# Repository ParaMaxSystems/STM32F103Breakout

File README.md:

# STM32F103Breakout
STM32 Breakout Board with Power Stage, inspired by Phil's Lab's design. 
STM32F103C8T board with connectors for I2C, USB, SPI, and GPIO headers.
Broken out to fit vertical or horizontal connectors.
Powered by a 3.3v switching regulator, taking power from USB or Vin and
conrverting to a 3.3v power source. Can be much smaller but I don't want to.

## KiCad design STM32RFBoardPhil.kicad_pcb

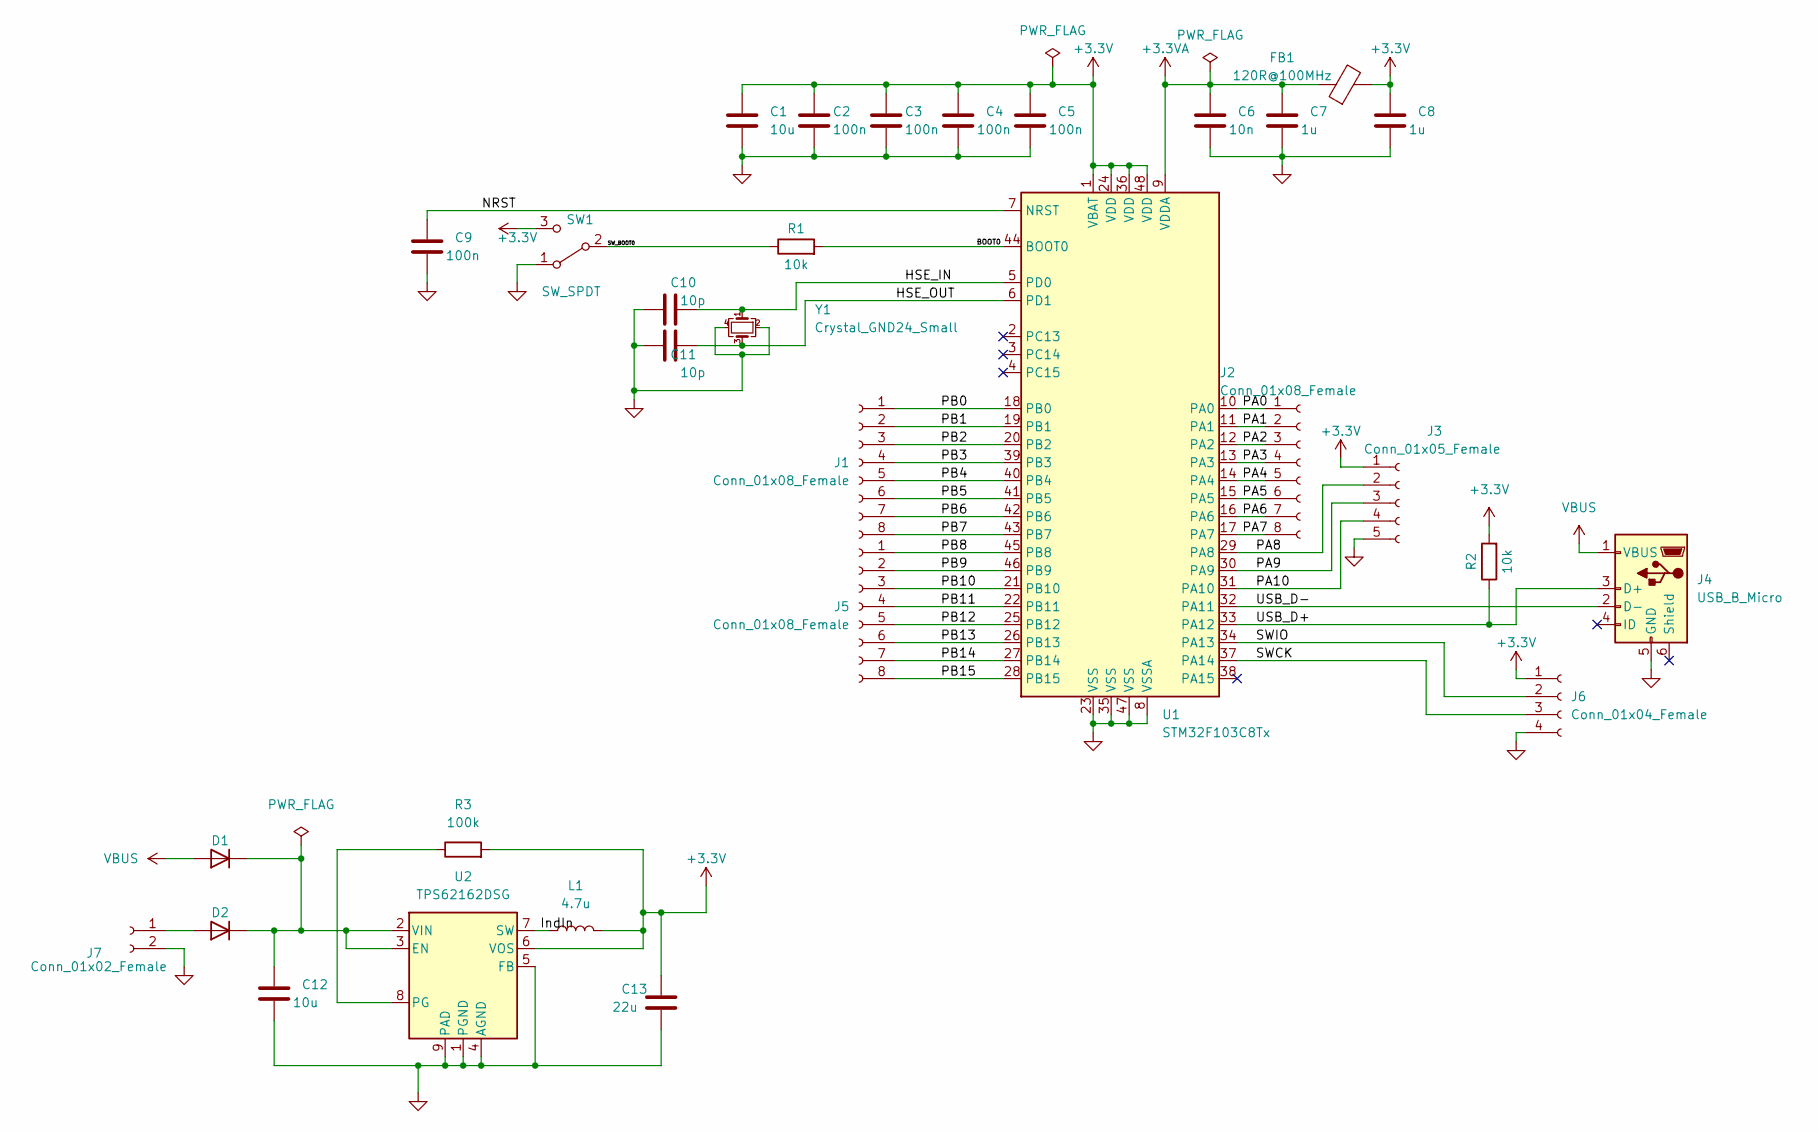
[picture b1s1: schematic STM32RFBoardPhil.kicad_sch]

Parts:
C1: 10u; C_0805_2012Metric
C2, C3, C4, C5, C9: 100n; C_0402_1005Metric
C6: 10n; C_0402_1005Metric
C7, C8: 1u; C_0402_1005Metric
C10, C11: 10p; C_0402_1005Metric
C12: 10u; C_0603_1608Metric
C13: 22u; C_0603_1608Metric
D1, D2: DIODE; D_0603_1608Metric
FB1: 120R@100MHz; L_0603_1608Metric
J1, J2, J5: Conn_01x08_Female; PinSocket_1x08_P2.54mm_Horizontal
J3: Conn_01x05_Female; PinSocket_1x05_P2.54mm_Horizontal
J4: USB_B_Micro; USB_Micro-B_Wuerth_629105150521
J6: Conn_01x04_Female; PinSocket_1x04_P2.54mm_Horizontal
J7: Conn_01x02_Female; PinSocket_1x02_P2.54mm_Vertical
L1: 4.7u; L_0805_2012Metric
R1, R2: 10k; R_0402_1005Metric
R3: 100k; R_0402_1005Metric
SW1: SW_SPDT; SW_SPDT_CK-JS102011SAQN
U1: STM32F103C8Tx; LQFP-48_7x7mm_P0.5mm
U2: TPS62162DSG; WSON-8-1EP_2x2mm_P0.5mm_EP0.9x1.6mm_ThermalVias
Y1: Crystal_GND24_Small; Crystal_SMD_3225-4Pin_3.2x2.5mm

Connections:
+3.3V: C1.1, C2.1, C3.1, C4.1, C5.1, C8.1, C13.1, FB1.2, J3.1, J6.1, L1.2, R2.2, R3.2, SW1.3 (C), U1.1 (VBAT), U1.24 (VDD), U1.36 (VDD), U1.48 (VDD), U2.6 (VOS)
+3.3VA: C6.1, C7.1, FB1.1, U1.9 (VDDA)
/BOOT0: R1.2, U1.44 (BOOT0)
/HSE_IN: C10.2, U1.5 (PD0), Y1.1
/HSE_OUT: C11.2, U1.6 (PD1), Y1.3
/IndIn: L1.1, U2.7 (SW)
/NRST: C9.1, U1.7 (NRST)
/PA0: J2.1, U1.10 (PA0)
/PA1: J2.2, U1.11 (PA1)
/PA2: J2.3, U1.12 (PA2)
/PA3: J2.4, U1.13 (PA3)
/PA4: J2.5, U1.14 (PA4)
/PA5: J2.6, U1.15 (PA5)
/PA6: J2.7, U1.16 (PA6)
/PA7: J2.8, U1.17 (PA7)
/PA8: J3.2, U1.29 (PA8)
/PA9: J3.3, U1.30 (PA9)
/PA10: J3.4, U1.31 (PA10)
/PB0: J1.1, U1.18 (PB0)
/PB1: J1.2, U1.19 (PB1)
/PB2: J1.3, U1.20 (PB2)
/PB3: J1.4, U1.39 (PB3)
/PB4: J1.5, U1.40 (PB4)
/PB5: J1.6, U1.41 (PB5)
/PB6: J1.7, U1.42 (PB6)
/PB7: J1.8, U1.43 (PB7)
/PB8: J5.1, U1.45 (PB8)
/PB9: J5.2, U1.46 (PB9)
/PB10: J5.3, U1.21 (PB10)
/PB11: J5.4, U1.22 (PB11)
/PB12: J5.5, U1.25 (PB12)
/PB13: J5.6, U1.26 (PB13)
/PB14: J5.7, U1.27 (PB14)
/PB15: J5.8, U1.28 (PB15)
/SWCK: J6.3, U1.37 (PA14)
/SWIO: J6.2, U1.34 (PA13)
/SW_BOOT0: R1.1, SW1.2 (B)
/USB_D+: J4.3 (D+), R2.1, U1.33 (PA12)
/USB_D-: J4.2 (D-), U1.32 (PA11)
GND: C1.2, C2.2, C3.2, C4.2, C5.2, C6.2, C7.2, C8.2, C9.2, C10.1, C11.1, C12.2, C13.2, J3.5, J4.5 (GND), J6.4, J7.2, SW1.1 (A), U1.8 (VSSA), U1.23 (VSS), U1.35 (VSS), U1.47 (VSS), U2.1 (PGND), U2.4 (AGND), U2.5 (FB), U2.9 (PAD), Y1.2, Y1.4
unnamed: D2.1 (A), J7.1
unnamed: R3.1, U2.8 (PG)
unnamed: C12.1, D1.2 (K), D2.2 (K), U2.2 (VIN), U2.3 (EN)
VBUS: D1.1 (A), J4.1 (VBUS)

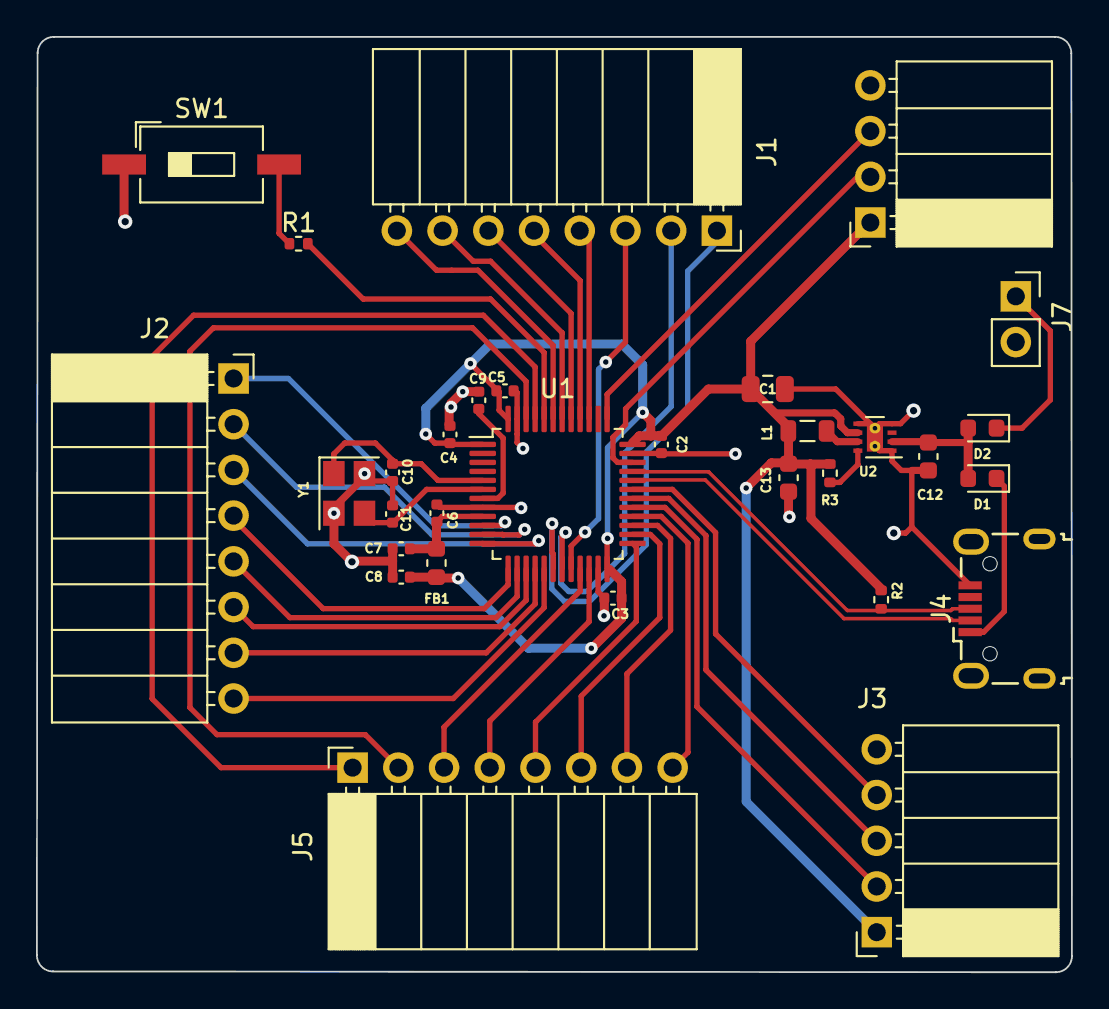
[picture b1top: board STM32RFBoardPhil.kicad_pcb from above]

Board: 2 copper layers, 57.5 x 52.0 mm, 31 parts (0 on the bottom side), 44 nets.

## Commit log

2022-10-28 Dropped the stuff
2022-10-28 Created README
2022-10-28 Uploaded GERBERS
